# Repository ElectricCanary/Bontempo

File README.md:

The Bontempo is a Tap Tempo & Modulation solution for PT2399 delay

Website : https://electric-canary.com/bontempo

Support : support@electric-canary.com

Perf & PCB by storyboardist : http://effectslayouts.blogspot.com/2021/02/bomtempo.html

The Code, Schematic and PCB manufacturing files are shared under a BY-NC-SA Creative Commons License

Go here for complete license : https://creativecommons.org/licenses/by-nc-sa/4.0/legalcode

Please reach out for licencing if you want to use the code in a commercial product.

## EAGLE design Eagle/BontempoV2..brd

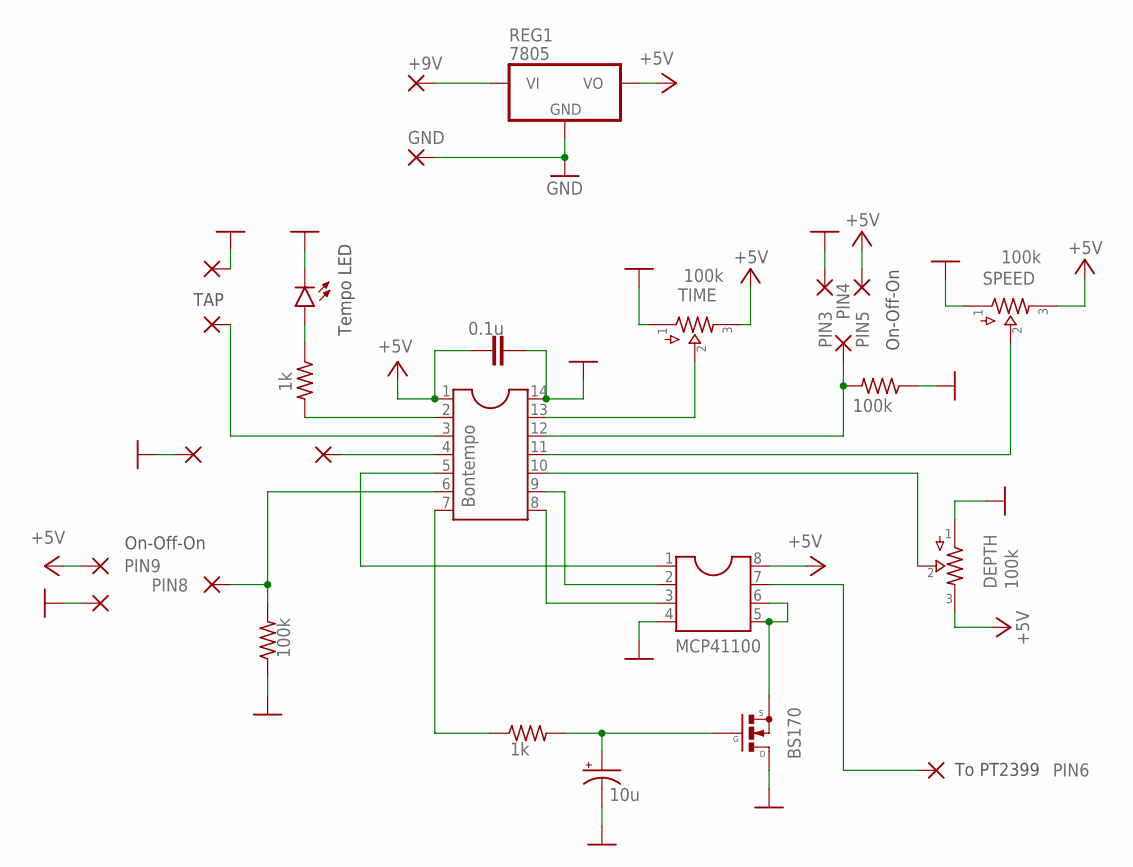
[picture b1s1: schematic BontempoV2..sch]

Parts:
+9V: 2,54/1,1
C1: 10u; 050_020
C2: 0.1u; BOX_SMALL
D1: LED3MM
DEPTH: 100k; PADS_SMALL
GND: 2,54/1,1
IC1: Bontempo; DIL14
IC2: MCP41100; DIL08
PIN1, PIN2, PIN3, PIN4, PIN5, PIN6, PIN7, PIN8, PIN9, PIN11, PIN12: 2,54/1,1
Q1: BS170; SOT54ES
R1, R3: 1k; R0207/3
R4, R5: 100k; R0207/3
REG1: 7805; TO92-
SPEED: 100k; PADS_SMALL
TIME: 100k; PADS_SMALL

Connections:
+5V: C2.1, DEPTH.3, IC1.1, IC2.8, PIN5.1, PIN9.1, REG1.3 (VO), SPEED.3, TIME.3
GND: C1.-, C2.2, D1.K (C), DEPTH.1, GND.1, IC1.14, IC2.4, PIN2.1, PIN3.1, PIN7.1, PIN11.1, Q1.D, R4.1, R5.1, REG1.2 (GND), SPEED.1, TIME.1
unnamed: IC1.2, R1.2
unnamed: IC2.5, IC2.6, Q1.S
unnamed: IC1.9, IC2.2
unnamed: IC1.8, IC2.3
unnamed: D1.A, R1.1
unnamed: IC1.4, PIN12.1
unnamed: IC1.3, PIN1.1
unnamed: C1.+, Q1.G, R3.2
unnamed: IC1.7, R3.1
unnamed: IC1.5, IC2.1
unnamed: IC1.6, PIN8.1, R4.2
unnamed: IC1.13, TIME.2
unnamed: IC1.11, SPEED.2
unnamed: IC1.12, PIN4.1, R5.2
unnamed: DEPTH.2, IC1.10
unnamed: +9V.1, REG1.1 (VI)
unnamed: IC2.7, PIN6.1

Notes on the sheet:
On-Off-On
To PT2399
Tempo LED
TAP

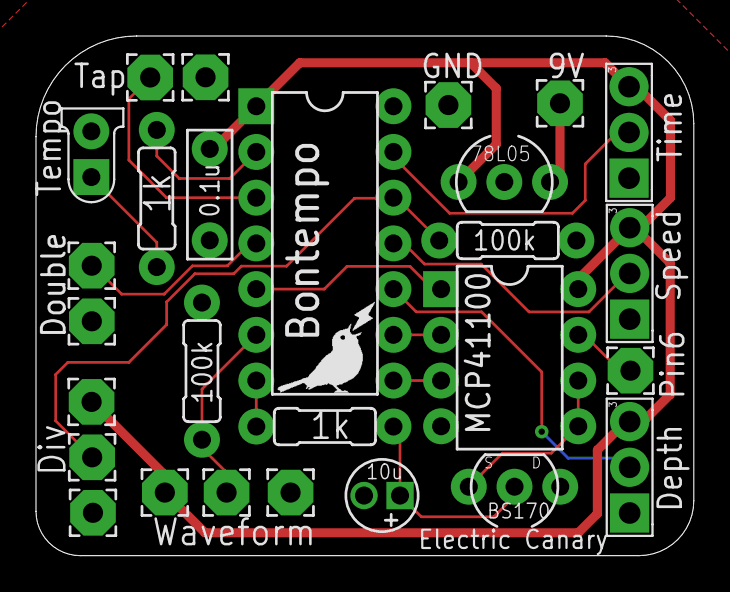
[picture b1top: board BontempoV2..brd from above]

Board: 2 copper layers, 36.5 x 28.9 mm, 27 parts (0 on the bottom side), 19 nets.

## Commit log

2020-06-30 Rename Bontempo_main.c.c to Bontempo_main.c
2023-06-25 Added Eagle and doc sources
